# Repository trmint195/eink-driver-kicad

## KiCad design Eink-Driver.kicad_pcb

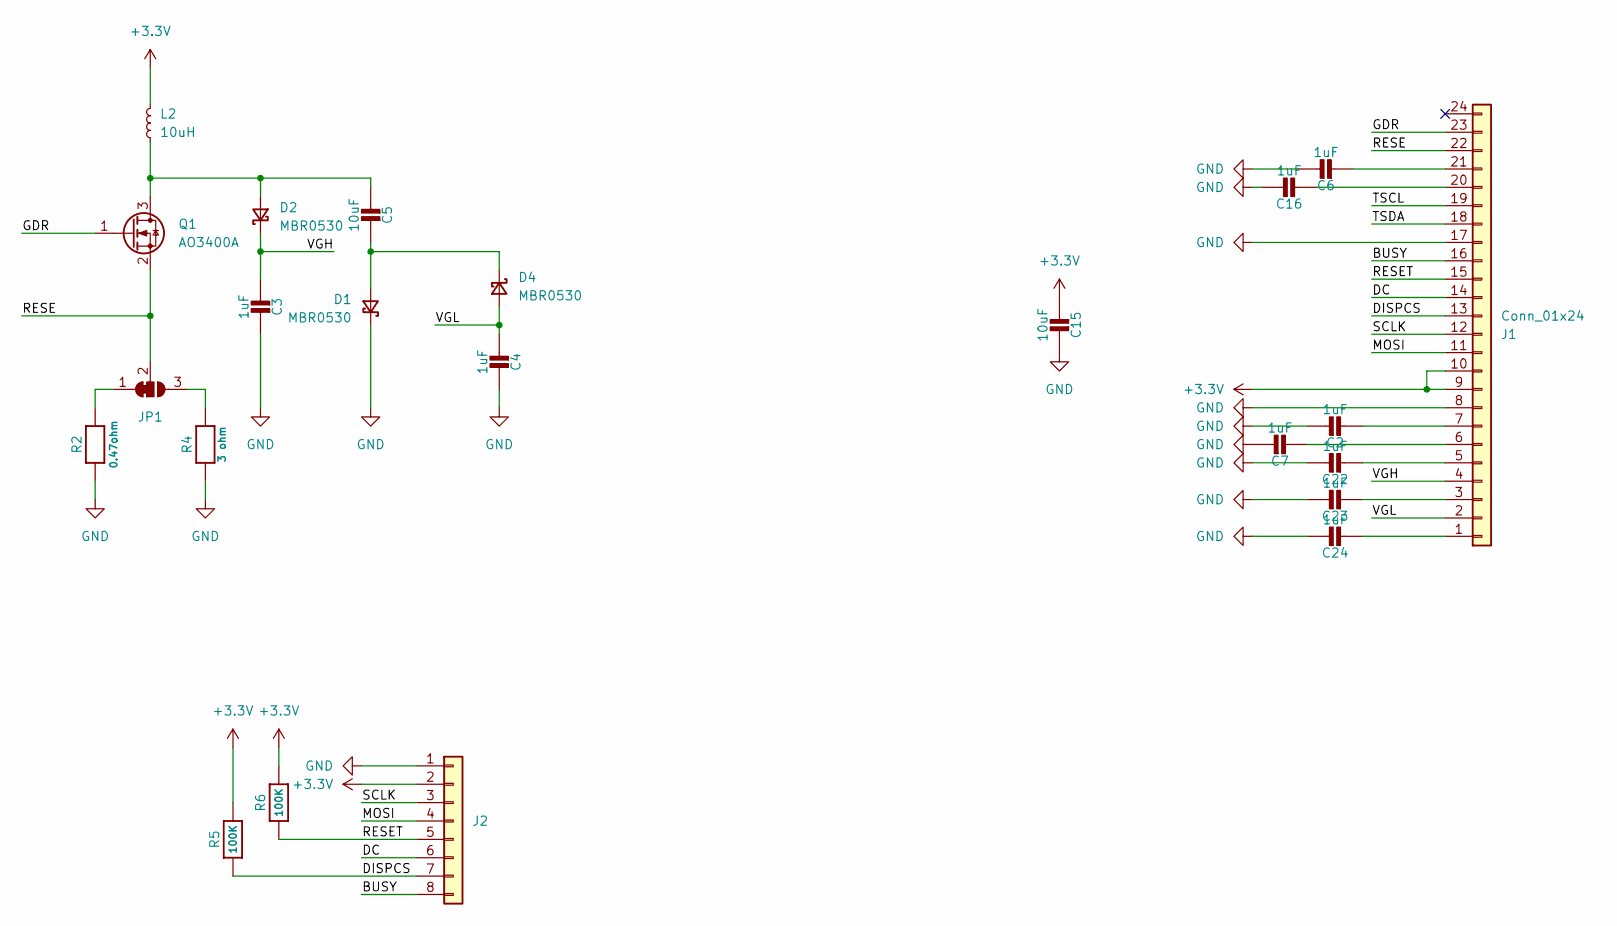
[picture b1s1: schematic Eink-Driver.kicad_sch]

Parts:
C2, C3, C4, C6, C7, C16, C22, C23, C24: 1uF; C_0603_1608Metric_Pad1.08x0.95mm_HandSolder
C5, C15: 10uF; C_0603_1608Metric_Pad1.08x0.95mm_HandSolder
D1, D2, D4: MBR0530; D_SOD-323_HandSoldering
J1: Conn_01x24; Amphenol_F32Q-1A7x1-11024_1x24-1MP_P0.5mm_Horizontal
J2: PinHeader_1x08_P2.54mm_Horizontal
JP1: SolderJumper-3_P1.3mm_Bridged12_RoundedPad1.0x1.5mm
L2: 10uH; L_Ferrocore_DLG-0403
Q1: AO3400A; SOT-23_Handsoldering
R2: 0.47ohm; R_0805_2012Metric
R4: 3 ohm; R_0805_2012Metric
R5, R6: 100K; R_0603_1608Metric_Pad0.98x0.95mm_HandSolder

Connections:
+3.3V: C15.2, J1.9, J1.10, J2.2, L2.2, R5.2, R6.2
/BUSY: J1.16, J2.8
/DC: J1.14, J2.6
/DISPCS: J1.13, J2.7, R5.1
/GDR: J1.23, Q1.1 (G)
/MOSI: J1.11, J2.4
/RESE: J1.22, JP1.2 (C), Q1.2 (S)
/RESET: J1.15, J2.5, R6.1
/SCLK: J1.12, J2.3
/TSCL: J1.19
/TSDA: J1.18
/VGH: C3.1, D2.1 (K), J1.4
/VGL: C4.1, D4.2 (A), J1.2
GND: C2.1, C3.2, C4.2, C6.1, C7.1, C15.1, C16.1, C22.1, C23.1, C24.1, D1.1 (K), J1.8, J1.17, J2.1, R2.2, R4.2
unnamed: C5.2, D1.2 (A), D4.1 (K)
unnamed: C5.1, D2.2 (A), L2.1, Q1.3 (D)
unnamed: C24.2, J1.1
unnamed: C23.2, J1.3
unnamed: C22.2, J1.5
unnamed: C7.2, J1.6
unnamed: C2.2, J1.7
unnamed: C16.2, J1.20
unnamed: C6.2, J1.21
unnamed: JP1.1 (A), R2.1
unnamed: JP1.3 (B), R4.1

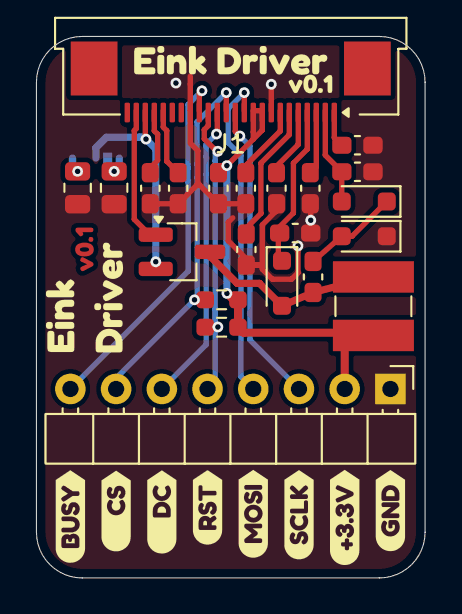
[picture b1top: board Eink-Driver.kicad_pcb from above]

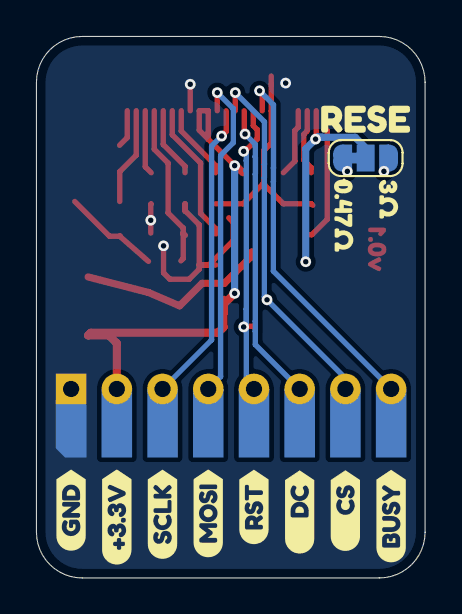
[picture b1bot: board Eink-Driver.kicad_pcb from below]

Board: 2 copper layers, 21.6 x 30.1 mm, 46 parts (12 on the bottom side), 23 nets.

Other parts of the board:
kibuzzard-6A014E61: G***; kibuzzard-6A014E61
kibuzzard-6A03540B: G***; kibuzzard-6A03540B
kibuzzard-69633CA3, kibuzzard-69633CA3#2: G***; kibuzzard-69633CA3
kibuzzard-69635A23: G***; kibuzzard-69635A23
kibuzzard-696332CC: G***; kibuzzard-696332CC
kibuzzard-696332E8: G***; kibuzzard-696332E8
kibuzzard-696357B1, kibuzzard-696357B1#2: G***; kibuzzard-696357B1
kibuzzard-696357DA: G***; kibuzzard-696357DA
kibuzzard-696359C0: G***; kibuzzard-696359C0
kibuzzard-6963572A, kibuzzard-6963572A#2: G***; kibuzzard-6963572A
kibuzzard-6963574A, kibuzzard-6963574A#2: G***; kibuzzard-6963574A
kibuzzard-6963576B, kibuzzard-6963576B#2: G***; kibuzzard-6963576B
kibuzzard-6963580C: G***; kibuzzard-6963580C
kibuzzard-69634677: G***; kibuzzard-69634677
kibuzzard-69635758, kibuzzard-69635758#2: G***; kibuzzard-69635758
kibuzzard-69635784, kibuzzard-69635784#2: G***; kibuzzard-69635784

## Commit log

2026-05-12 init
